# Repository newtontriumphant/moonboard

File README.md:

# moonboard, by zsharpminor!

Hi there and welcome! This is moonboard - a custom RP2040-powered devboard with an integrated temperature sensor and a status LED. Surprisingly, it's fully functional first-attempt and isn't (yet!) acting as a hot plate.

# Design:

I made this project to get experience wiring tight spaces in KiCad - my first time wiring a non-premade MCU.

### Schematic

### PCB

(front)

(back)

(silkscreen front)

(silkscreen back)

### 3D RENDERS OF PCB

(front)

(back)

### JLCPCB IMAGES:

**LINK TO ONLINE BOM**: https://docs.google.com/spreadsheets/d/1HLCWrT6yZXuZGsytFHmTzsnE9zg9GKQJlMwihE3njsE/

(BOM.csv file also attached in PCB folder).

# Build:

**A video demo of the completed build can be found here:** https://youtube.com/shorts/RiM_gK4lOYQ

(front!!)

(back ;w;)

(bootloader working first try!!)

(test board working!! yay!!)

(simple boring polyrhythm test code!!)

Thanks for reading up to here, you get a cookie! 🍪 :D

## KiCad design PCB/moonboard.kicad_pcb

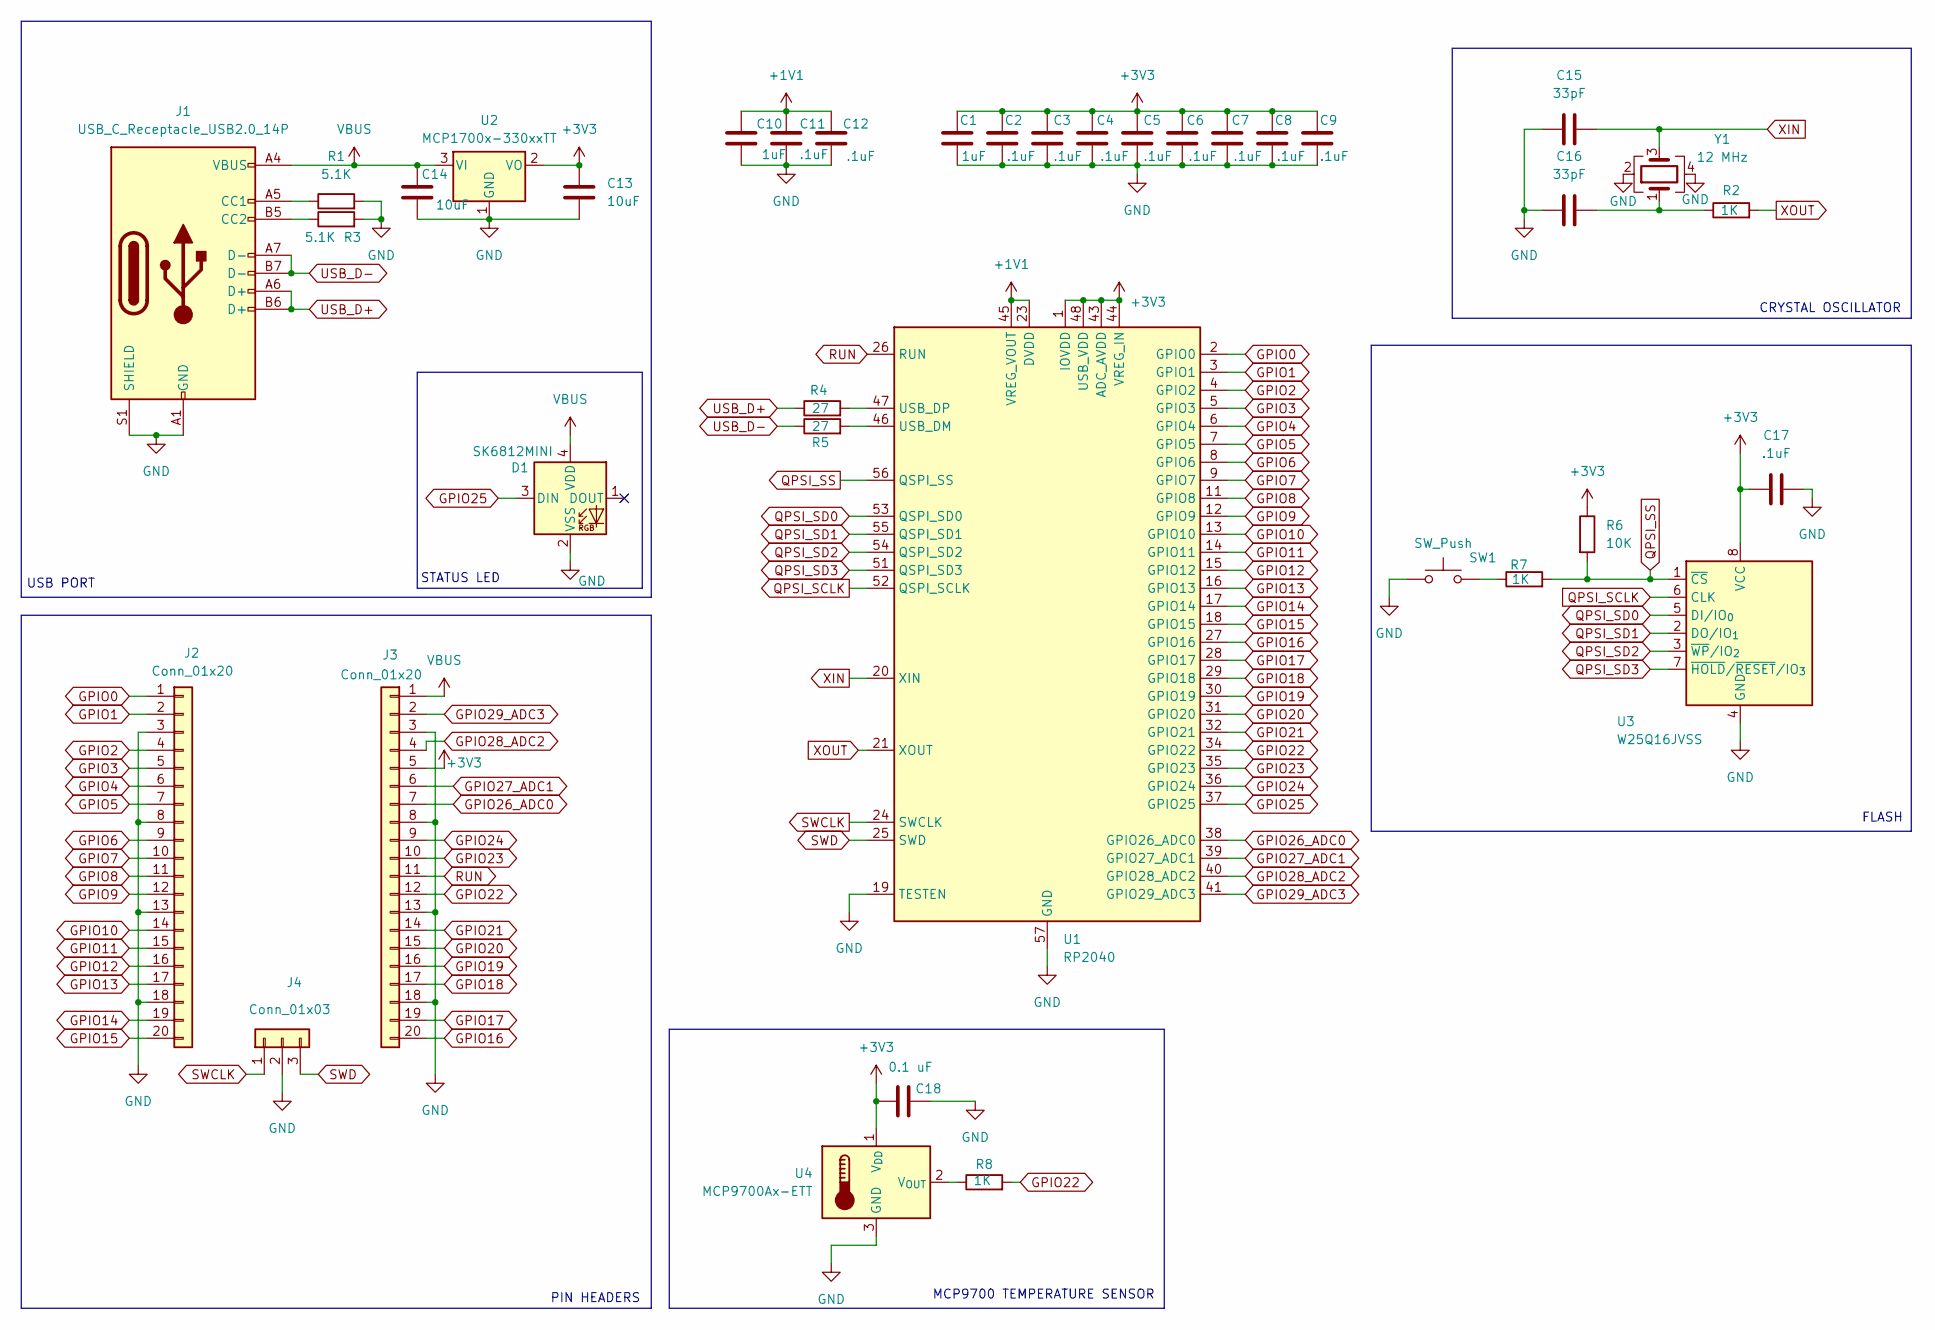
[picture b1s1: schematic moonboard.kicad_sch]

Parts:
C1, C3, C4, C5, C6, C7, C8, C9, C11, C12, C17: .1uF; C_0402_1005Metric
C2, C10: 1uF; C_0402_1005Metric
C13, C14: 10uF; C_0402_1005Metric
C15, C16: 33pF; C_0402_1005Metric
C18: 0.1 uF; C_0402_1005Metric
D1: SK6812MINI; LED_SK6812MINI_PLCC4_3.5x3.5mm_P1.75mm
J1: USB_C_Receptacle_USB2.0_14P; USB_C_Receptacle_HRO_TYPE-C-31-M-12
J2, J3: Conn_01x20; PinHeader_1x20_P2.54mm_Vertical
J4: Conn_01x03; PinHeader_1x03_P2.54mm_Vertical
R1, R3: 5.1K; R_0402_1005Metric
R2, R7, R8: 1K; R_0402_1005Metric
R4, R5: 27; R_0402_1005Metric
R6: 10K; R_0402_1005Metric
SW1: SW_Push; SW_Push_SPST_NO_Alps_SKRK
U1: RP2040; QFN-56-1EP_7x7mm_P0.4mm_EP3.2x3.2mm
U2: MCP1700x-330xxTT; SOT-23
U3: W25Q16JVSS; Winbond_USON-8-1EP_3x2mm_P0.5mm_EP0.2x1.6mm
U4: MCP9700Ax-ETT; SOT-23
Y1: 12 MHz; Crystal_SMD_3225-4Pin_3.2x2.5mm

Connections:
+1V1: C10.1, C11.1, C12.1, U1.23 (DVDD), U1.45 (VREG_VOUT), U1.50 (DVDD)
+3V3: C1.1, C2.1, C3.1, C4.1, C5.1, C6.1, C7.1, C8.1, C9.1, C13.1, C17.1, C18.1, J3.5, R6.1, U1.1 (IOVDD), U1.10 (IOVDD), U1.22 (IOVDD), U1.33 (IOVDD), U1.42 (IOVDD), U1.43 (ADC_AVDD), U1.44 (VREG_IN), U1.48 (USB_VDD), U1.49 (IOVDD), U2.2 (VO), U3.8 (VCC), U4.1 (V_{DD})
GND: C1.2, C2.2, C3.2, C4.2, C5.2, C6.2, C7.2, C8.2, C9.2, C10.2, C11.2, C12.2, C13.2, C14.2, C15.1, C16.1, C17.2, C18.2, D1.2 (VSS), J1.A1 (GND), J1.A12 (GND), J1.B1 (GND), J1.B12 (GND), J1.S1 (SHIELD), J2.3, J2.8, J2.13, J2.18, J3.3, J3.8, J3.13, J3.18, J4.2, R1.2, R3.2, SW1.1, U1.19 (TESTEN), U1.57 (GND), U2.1 (GND), U3.4 (GND), U4.3 (GND), Y1.2, Y1.4
GPIO0: J2.1, U1.2 (GPIO0)
GPIO1: J2.2, U1.3 (GPIO1)
GPIO2: J2.4, U1.4 (GPIO2)
GPIO3: J2.5, U1.5 (GPIO3)
GPIO4: J2.6, U1.6 (GPIO4)
GPIO5: J2.7, U1.7 (GPIO5)
GPIO6: J2.9, U1.8 (GPIO6)
GPIO7: J2.10, U1.9 (GPIO7)
GPIO8: J2.11, U1.11 (GPIO8)
GPIO9: J2.12, U1.12 (GPIO9)
GPIO10: J2.14, U1.13 (GPIO10)
GPIO11: J2.15, U1.14 (GPIO11)
GPIO12: J2.16, U1.15 (GPIO12)
GPIO13: J2.17, U1.16 (GPIO13)
GPIO14: J2.19, U1.17 (GPIO14)
GPIO15: J2.20, U1.18 (GPIO15)
GPIO16: J3.20, U1.27 (GPIO16)
GPIO17: J3.19, U1.28 (GPIO17)
GPIO18: J3.17, U1.29 (GPIO18)
GPIO19: J3.16, U1.30 (GPIO19)
GPIO20: J3.15, U1.31 (GPIO20)
GPIO21: J3.14, U1.32 (GPIO21)
GPIO22: J3.12, R8.2, U1.34 (GPIO22)
GPIO23: J3.10, U1.35 (GPIO23)
GPIO24: J3.9, U1.36 (GPIO24)
GPIO25: D1.3 (DIN), U1.37 (GPIO25)
GPIO26_ADC0: J3.7, U1.38 (GPIO26_ADC0)
GPIO27_ADC1: J3.6, U1.39 (GPIO27_ADC1)
GPIO28_ADC2: J3.4, U1.40 (GPIO28_ADC2)
GPIO29_ADC3: J3.2, U1.41 (GPIO29_ADC3)
unnamed: C16.2, R2.1, Y1.1
unnamed: J1.A5 (CC1), R1.1
unnamed: J1.B5 (CC2), R3.1
unnamed: R7.1, SW1.2
unnamed: R5.2, U1.46 (USB_DM)
unnamed: R4.2, U1.47 (USB_DP)
unnamed: R8.1, U4.2 (V_{OUT})
QPSI_SCLK: U1.52 (QSPI_SCLK), U3.6 (CLK)
QPSI_SD0: U1.53 (QSPI_SD0), U3.5 (DI/IO_{0})
QPSI_SD1: U1.55 (QSPI_SD1), U3.2 (DO/IO_{1})
QPSI_SD2: U1.54 (QSPI_SD2), U3.3 (~WP/IO_{2})
QPSI_SD3: U1.51 (QSPI_SD3), U3.7 (~HOLD/~RESET/IO_{3})
QPSI_SS: R6.2, R7.2, U1.56 (QSPI_SS), U3.1 (~CS)
RUN: J3.11, U1.26 (RUN)
SWCLK: J4.1, U1.24 (SWCLK)
SWD: J4.3, U1.25 (SWD)
USB_D+: J1.A6 (D+), J1.B6 (D+), R4.1
USB_D-: J1.A7 (D-), J1.B7 (D-), R5.1
VBUS: C14.1, D1.4 (VDD), J1.A4 (VBUS), J1.A9 (VBUS), J1.B4 (VBUS), J1.B9 (VBUS), J3.1, U2.3 (VI)
XIN: C15.2, U1.20 (XIN), Y1.3
XOUT: R2.2, U1.21 (XOUT)

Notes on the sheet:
MCP9700 TEMPERATURE SENSOR
USB PORT
PIN HEADERS
STATUS LED
FLASH
CRYSTAL OSCILLATOR

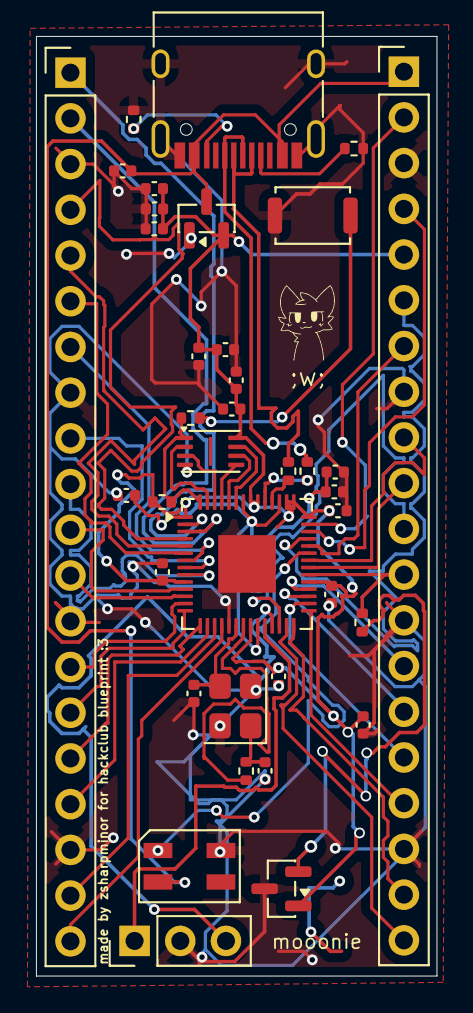
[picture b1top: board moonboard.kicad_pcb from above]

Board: 2 copper layers, 22.2 x 52.2 mm, 37 parts (0 on the bottom side), 54 nets.

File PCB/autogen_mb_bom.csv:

"Id";"Designator";"Footprint";"Quantity";"Designation";"Supplier and ref";
1;"C17,C11,C8,C3,C9,C4,C1,C7,C6,C12,C5";"C_0402_1005Metric";11;".1uF";;;
2;"C16,C15";"C_0402_1005Metric";2;"33pF";;;
3;"J1";"USB_C_Receptacle_HRO_TYPE-C-31-M-12";1;"USB_C_Receptacle_USB2.0_14P";;;
4;"U4";"SOT-23";1;"MCP9700Ax-ETT";;;
5;"U2";"SOT-23";1;"MCP1700x-330xxTT";;;
6;"C18";"C_0402_1005Metric";1;"0.1 uF";;;
7;"J3,J2";"PinHeader_1x20_P2.54mm_Vertical";2;"Conn_01x20";;;
8;"R8,R2,R7";"R_0402_1005Metric";3;"1K";;;
9;"C10,C2";"C_0402_1005Metric";2;"1uF";;;
10;"U3";"Winbond_USON-8-1EP_3x2mm_P0.5mm_EP0.2x1.6mm";1;"W25Q16JVSS";;;
11;"C14,C13";"C_0402_1005Metric";2;"10uF";;;
12;"D1";"LED_SK6812MINI_PLCC4_3.5x3.5mm_P1.75mm";1;"SK6812MINI";;;
13;"R5,R4";"R_0402_1005Metric";2;"27";;;
14;"J4";"PinHeader_1x03_P2.54mm_Vertical";1;"Conn_01x03";;;
15;"Y1";"Crystal_SMD_3225-4Pin_3.2x2.5mm";1;"12 MHz";;;
16;"R3,R1";"R_0402_1005Metric";2;"5.1K";;;
17;"SW1";"SW_Push_SPST_NO_Alps_SKRK";1;"SW_Push";;;
18;"U1";"QFN-56-1EP_7x7mm_P0.4mm_EP3.2x3.2mm";1;"RP2040";;;
19;"R6";"R_0402_1005Metric";1;"10K";;;

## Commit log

2025-12-10 Finalized Readme.
2025-12-10 Added PCB
2025-12-10 Added BOM.
2025-12-10 Added KiCad PCB Files.
2025-12-10 Added Gerbers.
2025-12-27 Final Changes!
2025-12-27 Final Changes!
    Rephrase a section of the README to clarify the purpose of the project and its educational value.
2025-12-27 Added New BOM!
2025-12-27 Revise BOM with pricing and update notes
    Updated the BOM to include prices and added a warning about the old BOM.
2025-12-27 Finalized BOM
2025-12-27 Added PCBA files.
2026-01-16 Added Polyrhythm Test Code
2026-01-16 Updated README.md for Build Review!
    Added build section with demo video and images.
2026-05-05 Update README.
